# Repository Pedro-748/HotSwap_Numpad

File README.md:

Custom designed Open-Source Numpad/Macropad
I needed a numpad, more specifically a 10 key pad with Backspace and Tab for work. Now I considered simply settling with remapping a existing numpad in QMK, which of course is totally possible and if you found this because you have this problem... Just do that. it will save you 10s of hours, and alot of money. Or use these files and save the time, but you will likely still end up spending 2-3x the cost of a really nice off the shelf numpad. I might link some here sometime, because unless a few dozen of you decide to put this into GB, it is simply not worth the investment. Thus, contining to read this "Readme" is really not worth your time, or mine to write it, But hey! I'm already this far... (and so are you, so once more go buy a numpad but feel free to see how far this devolves from here.)

	Key Features: 
Optional Top Row Layout: 1.5u Backspace/ 1.5u Tab

Optional Bottom Row ("0, ."): 1.75u Shift/ 1.25u Fn

No Vertical 2u "+" swapped for 2 additional 1u keys

	Future Updates:
 For Absolutly no reason, I have decided I want it to also have the option of adding a OLED/LCD Screen and Wireless functionality (depending on Microcontroller compatability) and so I will be figuring out how to add a battery jack, and 5 pin connector. 
 
 Once I get the first Prototypes from my solder version (see /Custom_Numpad1) I will begin building the firmware.

 Current Plan is to support MOST popular micro controllers, which will require QMK/KMK/and ZMK, I have never done this from scratch so we shall see just how over ambitiuos this is. I have already obtained a Pi Pico (rp2040), Nice!Nano (nRF52840), and Pro Micro (ATmega32U4). 

 Depending on how that goes, I plan to design another PCB with integrated microcontroller, TBD.

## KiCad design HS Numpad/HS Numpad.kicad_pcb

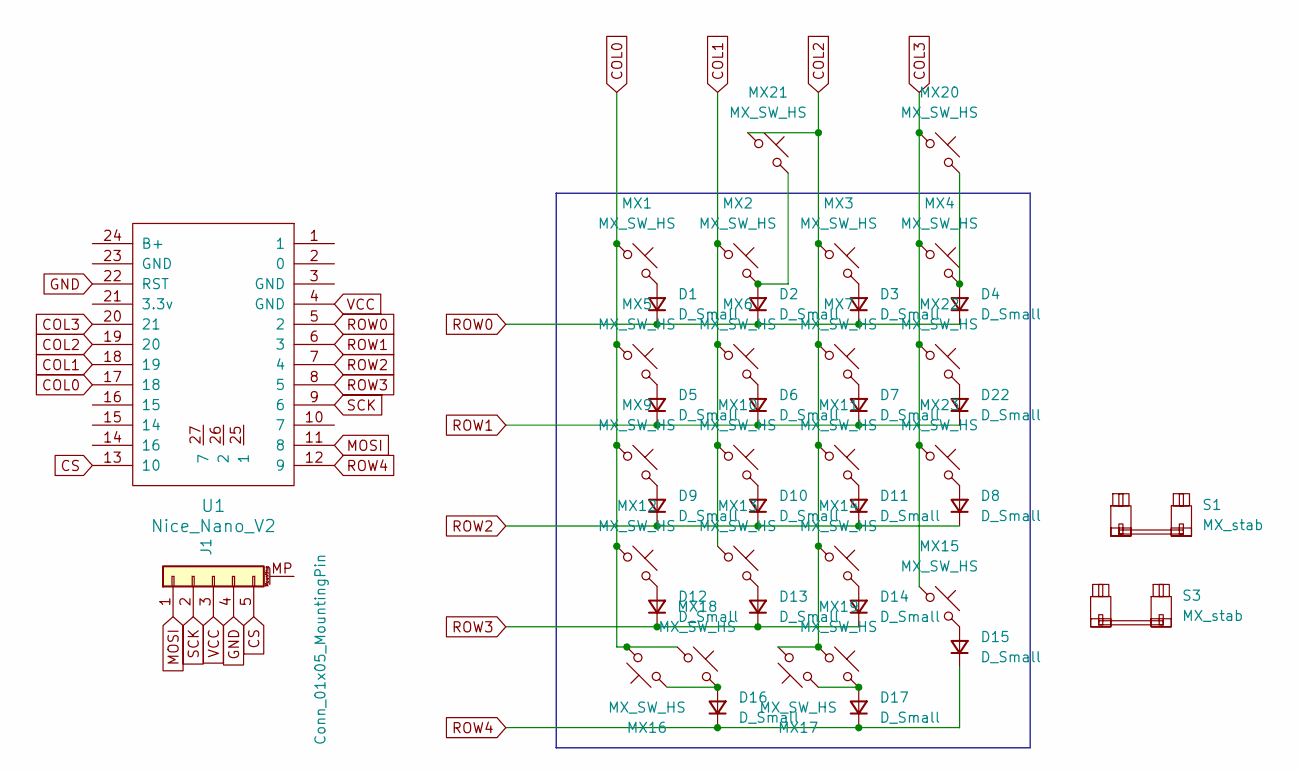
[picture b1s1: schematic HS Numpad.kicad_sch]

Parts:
D1, D2, D3, D4, D5, D6, D7, D8, D9, D10, D11, D12, D13, D14, D15, D16, D17, D22: D_Small; Diode_SOD-123
J1: Conn_01x05_MountingPin
MX1, MX2, MX3, MX4, MX5, MX6, MX7, MX9, MX10, MX11, MX12, MX13, MX14, MX15, MX16, MX17, MX22, MX23: MX_SW_HS; SW_MX_HS_CPG151101S11_1u
MX18: MX_SW_HS; SW_MX_HS_CPG151101S11_1.75u
MX19: MX_SW_HS; SW_MX_HS_CPG151101S11_1.25u
MX20, MX21: MX_SW_HS; SW_MX_HS_CPG151101S11_1.5u
S1, S3: MX_stab; STAB_MX_2u
U1: Nice_Nano_V2

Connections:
COL0: MX1.1, MX5.1, MX9.1, MX12.1, MX16.2, MX18.1, U1.17 (18)
COL1: MX2.1, MX6.1, MX10.1, MX13.1, U1.18 (19)
COL2: MX3.1, MX7.1, MX11.1, MX14.1, MX17.2, MX19.1, MX21.1, U1.19 (20)
COL3: MX4.1, MX15.1, MX20.1, MX22.1, MX23.1, U1.20 (21)
CS: J1.5, U1.13 (10)
GND: J1.4, U1.22 (RST)
MOSI: J1.1, U1.11 (8)
unnamed: D1.2 (A), MX1.2
unnamed: D2.2 (A), MX2.2, MX21.2
unnamed: D3.2 (A), MX3.2
unnamed: D4.2 (A), MX4.2, MX20.2
unnamed: D5.2 (A), MX5.2
unnamed: D6.2 (A), MX6.2
unnamed: D7.2 (A), MX7.2
unnamed: D8.2 (A), MX23.2
unnamed: D9.2 (A), MX9.2
unnamed: D10.2 (A), MX10.2
unnamed: D11.2 (A), MX11.2
unnamed: D12.2 (A), MX12.2
unnamed: D13.2 (A), MX13.2
unnamed: D14.2 (A), MX14.2
unnamed: D15.2 (A), MX15.2
unnamed: D16.2 (A), MX16.1, MX18.2
unnamed: D17.2 (A), MX17.1, MX19.2
unnamed: D22.2 (A), MX22.2
ROW0: D1.1 (K), D2.1 (K), D3.1 (K), D4.1 (K), U1.5 (2)
ROW1: D5.1 (K), D6.1 (K), D7.1 (K), D22.1 (K), U1.6 (3)
ROW2: D8.1 (K), D9.1 (K), D10.1 (K), D11.1 (K), U1.7 (4)
ROW3: D12.1 (K), D13.1 (K), D14.1 (K), U1.8 (5)
ROW4: D15.1 (K), D16.1 (K), D17.1 (K), U1.12 (9)
SCK: J1.2, U1.9 (6)
VCC: J1.3, U1.4 (GND)

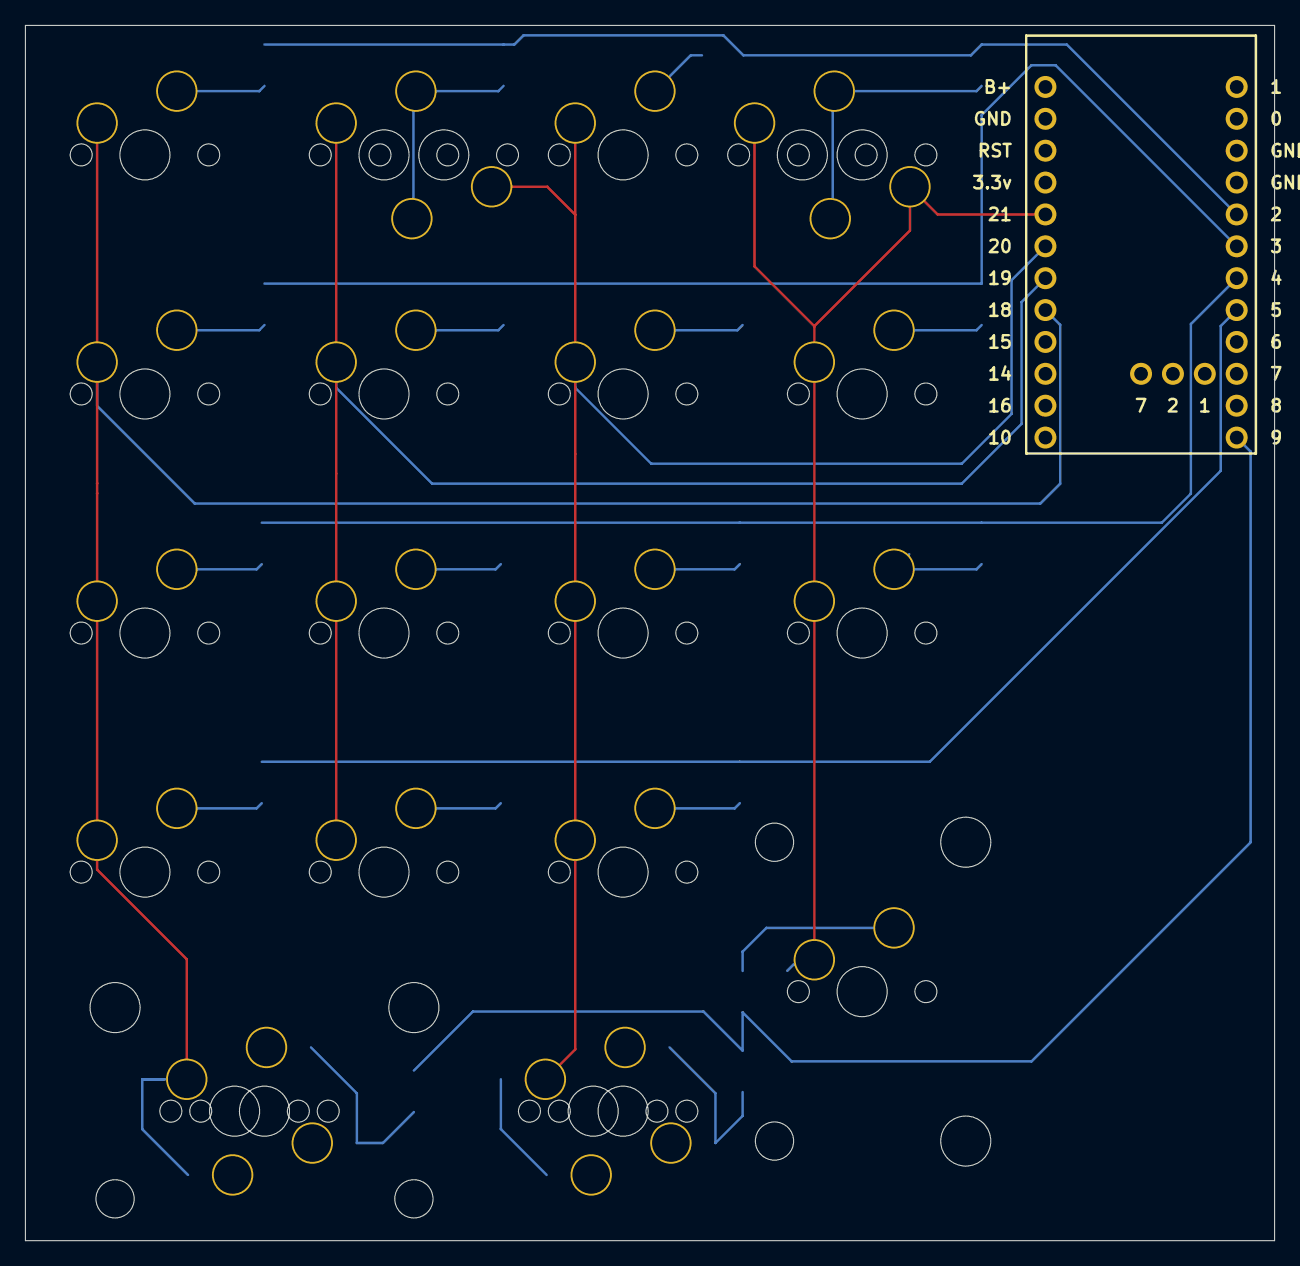
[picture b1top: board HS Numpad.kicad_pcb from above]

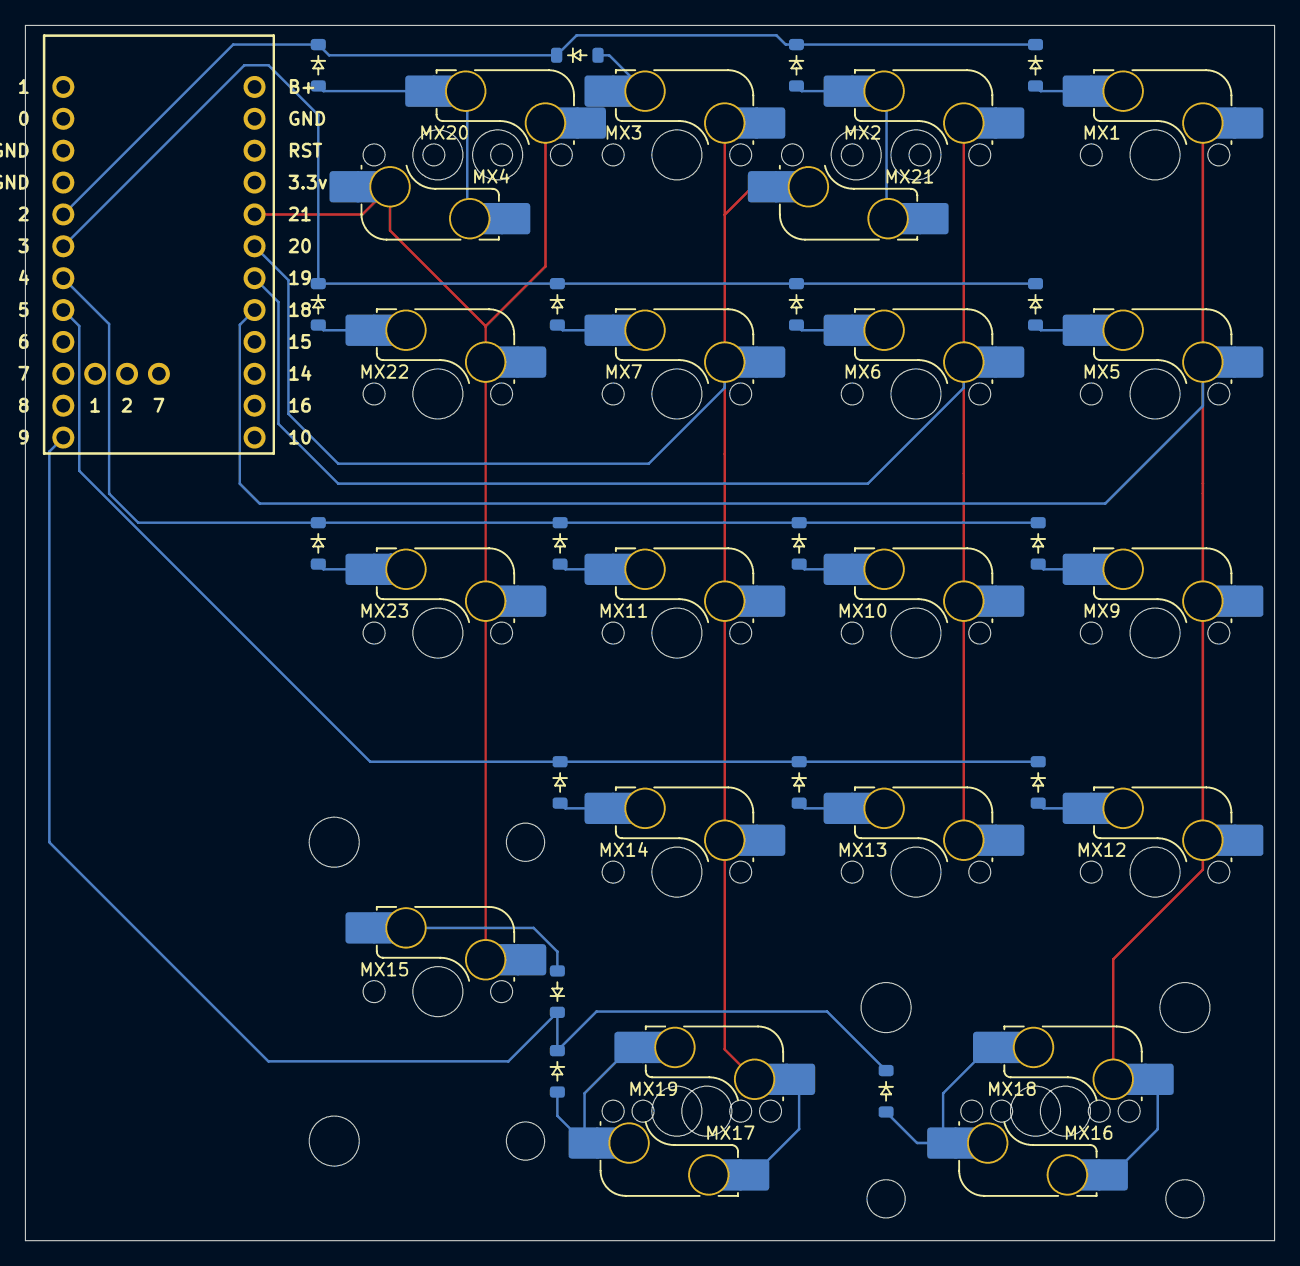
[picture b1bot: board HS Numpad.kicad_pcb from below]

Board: 2 copper layers, 99.5 x 96.8 mm, 43 parts (41 on the bottom side), 27 nets.

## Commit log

2024-06-15 HS Numpad/Alt Layout
